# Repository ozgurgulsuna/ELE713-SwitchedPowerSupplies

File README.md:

# INTRODUCTION

This report presents the design and implementation of a forward converter that operates with an input voltage range of 36-60 V DC, providing a primary output of 5 V at 8 A along with a secondary auxiliary output of 12 V at 4 W. The forward converter is a type of DC-to-DC converter that transfers power during the forward operation of a transformer, making it suitable for applications requiring isolated and regulated outputs.

To achieve precise control over the output voltage, the design employs an analog controller integrated with a feedforward loop. The primary side of the converter utilizes a single switch, while the transformer flux is reset using an additional winding and a diode. This approach ensures efficient operation and prevents magnetic saturation of the transformer core.

In low-voltage, high-current applications, traditional diode-based rectification becomes less efficient due to the voltage drop across the diodes, typically around 0.5 V. To address this inefficiency, synchronous rectification is implemented using MOSFETs at the output. When conducting, a MOSFET with a 10-milliohm resistance produces a voltage drop of only 0.1 V at 10 A, significantly improving overall efficiency.

The printed circuit board (PCB) for this design is manufactured using a photolithography process. This process includes applying a photoresistive UV coating and etching the copper layer using a solution of hydrogen peroxide and hydrochloric acid. The circuit's functionality is thoroughly tested under various load conditions, including overload scenarios and auxiliary load operation, to validate its performance and reliability.

This report further discusses the chosen topology, magnetic design, and key considerations in achieving an efficient, compact, and robust forward converter design.

| Specification        |          |
|--------------|-------|
| Input Voltage                   | 36-60 Vdc (Nominal 48Vdc)            |
| Main Output Voltage             | 5V (min. 4.9V, max. 5.1V)            |
| Output Voltage Ripple           | 100mV peak-to-peak                   |
| Main Output Nominal Current     | 8A                                   |
| Continuous Output Power         | 40W (Main Output)                    |
| Overload Current                | 9A                                   |
| Auxiliary Output Voltage        | 12V                                  |
| Auxiliary Output Nominal Current| 0.3A                                 |
| Auxiliary Output Power          | 4W                                   |
| Line Regulation                 | $\pm 0.2$%                           |
| Load Regulation                 | $\pm 0.5$%                           |
| Transient Peak Deviation        | 10% of Vout (10% load to 100% @ 48 V) |
| Transient Response Recovery     | 200 $\mu sec$ (10% load to 100% @ 48 V) |
| Overall Efficiency @ Full Load  |$\ge$ 80%                             |

---

# TOPOLOGY
The forward converter is a widely used topology in DC-to-DC conversion, especially for applications requiring electrical isolation and multiple outputs. This topology operates by transferring energy through a transformer during the on-state of the primary-side switch, with energy delivery controlled by the duty cycle of the switch. It is a buck-type converter implemented with the output LC filter structure.

*Schematic of Forward Converter*

The duty ratio, defined as the proportion of time the primary switch is on during a switching cycle, is a critical parameter in determining the output voltage of the forward converter. The relationship between the input voltage, duty ratio, and transformer turns ratio governs the output voltage. A feedback mechanism ensures the duty ratio is adjusted dynamically to maintain a stable output under varying input and load conditions. In a forward converter, the maximum duty cycle is required to be less than 50% to ensure the transformer reset.

$${V_o \over V_i} = {Ns\over Np}*D$$

At the first cycle when the transistor T is ON, the transformer transfers power to the secondary side, and reset winding is reverse biased. In the second cycle, reset winding resets the transformer and supplies the magnetizing current back to the supply, and the load is supplied by the inductor and capacitor. Reset winding is very important to reset to transformer to prevent core saturation. In our design, we need to add two more windings to the transformer, one is to supply the primary side control circuitry, and another is to create the required 12V auxiliary supply.

The forward converter design includes a bias supply for the primary side, which provides the necessary power to the control circuitry and auxiliary components. This supply is derived from the bias winding connected to the primary side. The circuit initially starts with a voltage divider and a zener diode. As the bias winding experiences a change in flux, it supplies the rest of the circuit with the required voltage. The output of the bias winding is configured as a rectifier of a forward converter and is regulated with a linear regulator constructed from an NPN transistor. This sets the bias supply to approximately 12 volts.

*Schematic of the Bias Voltage Generation Subcircuit.*

The secondary side of the converter includes an auxiliary output in addition to the primary output. This output is set to 12 volts and is rated for 0.3 amperes, resulting in a 4 W auxiliary output. The auxiliary output is supplied from another auxiliary winding with a forward rectifier output. This output is also regulated using a 12-volt linear regulator and is referenced to the ground of the secondary winding.

*Schematic of the Auxiliary Voltage Generation Subcircuit.*

---

# MAGNETIC DESIGN

Magnetic design is a critical aspect of the forward converter, as it directly impacts efficiency, size, and reliability. The transformer in the forward converter serves two primary purposes: providing electrical isolation and stepping the voltage up or down based on the turn ratio.

A forward converter utilizes a transformer operating in forward mode, meaning that energy is transferred directly through the transformer core during the on-state of the primary switch. Unlike some other topologies, energy is not stored in the core during one cycle and transferred in the next; instead, the transfer is immediate.

The magnetic design is done in a MATLAB script that calculates key parameters for a forward converter, focusing on component sizing and operational constraints. It starts by defining input/output voltage ranges, power requirements, efficiency assumptions, and ripple constraints. The output current and its ripple are calculated to establish operating boundaries.

A significant part of the script focuses on determining the duty cycle range as a function of the transformer turns ratio $$(\N_1/N_2\)$$ and selecting an optimal ratio to ensure the converter operates within specified limits. Transformer design calculations include determining winding turns for primary, secondary, and auxiliary windings while ensuring compliance with voltage and current constraints, such as switch voltage limits. The calculated turn ratios are given in the table below.

| Winding      | Turns |
|--------------|-------|
| Primary      | 10    |
| Reset        | 10    |
| Secondary    | 4     |
| Bias         | 7     |
| Auxiliary    | 7     |

*Selected Turns Ratios.*

The script calculates the magnetizing inductance $$\(L_m\)$$ and evaluates the impact of switching frequency on inductor performance. It also designs the output filter components to meet ripple voltage constraints.

Core selection is supported by area product $$\(A_p\)$$ calculations using various methods, ensuring the chosen core can handle the required flux and thermal limits. Wire gauge and winding distribution are calculated to balance current density and copper usage.

Finally, the script includes a loss analysis, estimating core and copper losses, and evaluating leakage inductance to ensure the design meets efficiency and performance goals. This approach focuses on key aspects of forward converter design while avoiding unnecessary complexity.

The code can be found in [magnetic design folder](%5B02%5D%20Magnetic%20Design/magnetic_design.m).

## TRANSFORMER REALIZATION ##

After evaluating the available cores, calculations are made, and a few candidate cores are chosen based on area product criteria. As a final decision, E30/15/7 3C94 is chosen (by Ferroxcube). There were smaller options; however, this core is favored considering the ease of implementation. Our switching frequency is chosen as 200kHz. At 200kHz, which is moderately high, we used $1 mm^2$ litz wires to avoid the skin effect and proximity effect. For the primary we have 10 turns with no parallel wires, at the secondary, we have 4 turns with 2 parallel wires. The auxiliary winding is winded using 0.2 $mm^2$ litz cable to have lower losses. Reset winding and primary bias circuitry are winded with thin copper cables so that they won't carry high currents. The order of windings is secondary-auxiliary-reset-bias-primary.

<div style="text-align: center;">
  
  <p><em>Transformer Windings Drawing</em></p>
</div>

---
# CONTROLLER DESIGN
For the controller, a specific analog integrated circuit, LT1952-1 produced by Analog Devices, is used to implement the controller. LT 1952-1 is a single-switch synchronous forward controller for forward controller designs within the range of 25-500 W. This controller is favored because it has the option to implement synchronous rectification. and high efficiencies can be achieved. LT1952 is the main controller; however, there are 2 more integrated circuits for the essential working of the converter. TL431 is used as a feedback compensator for controlling the output voltage. Moreover, LTC3900 is used for synchronous rectification which takes the SYNC signal from the LT1952-1 with the help of pulse transformer and switches two MOSFETs for improving the efficiency (with the risk of short-circuiting the secondary side MOSFETs).

---
# PRODUCTION AND ASSEMBLED PCB
The printed circuit board (PCB) for this design is manufactured using a photolithography process. This process includes applying a photoresistive UV coating and etching the copper layer using a solution of hydrogen peroxide and hydrochloric acid. The circuit's functionality is thoroughly tested under various load conditions, including overload scenarios and auxiliary load operation, to validate its performance and reliability.

<div style="text-align: center;">
  
  <p><em>Final Results of the etched PCB.</em></p>
</div>

<div style="text-align: center;">

  <p><em>Assembled PCB</em></p>
	        
</div>

## RESULTS ##
After the design is completed and assembled some measurements are taken. At first, some problems occurred at the current sense pin of the controller, which was due to a grounding problem. We solved it by fixing it. 

*Converter Output in the case of fault.*

After fixing that, tests were continued without synchronous switches which provided an efficiency of around 75%. We activated the synchronous rectification to increase efficiency and obtain better results. At this part, we had some problems with the synchronization and failed the synchronize both switches. However, synchronizing one switch had no disadvantage but a slight improvement so we obtained a  semi-synchronous converter. Forward converter without auxiliary is quite efficient; however, the auxiliary linear regulator creates quite a loss. The results are as follows:

*5V Rated Operation*

*Voltage Ripple Measurement*

Efficiency Calculations(@48V):

Only Forward Converter

${Efficiency} = {Pout \over Pin}$ =  $`{(5.15 × 7.21) \over (48.5 × 1.04)}`$ = 0.8602

Forward Converter with 4W auxiliary load

${Efficiency} = {Pout \over Pin}$ =  $`{(5.15 × 7.21 + 4.3) \over (48.5 × 1.04)}`$ = 0.8214

I would like to point out that @60V efficiency gets worse due to auxiliary efficiency. 

---

# CONCLUSION

In conclusion, there are several isolated DC-DC converter topologies with all their advantages
and disadvantages. In this project, forward converter topology is implemented to convert 36-
60V to 5V with the addition of 12V auxiliary voltage. Moreover, the project covers magnetic design, analog design, and feedback design
for isolated DC/DC converters. The design showed that the topology proved to be working;
however, there is still room for improvement in terms of PCB design, feedback design, and
magnetic design. 

---
# APPENDIX

```matlab
close all
clear 
clc
%% Specify project requirements

Vimax = 60;
Vimin = 36;
Vo = 5;
Po = 40;
Vaux = 12;
Paux = 4;

% Choose an estimated efficiency
eff_est = 0.82;

% Choose inductor ripple ratio (ismail wants this)
ripple_ratio = 0.1625;

% Voltage ripple defined by specifications
delta_Vo = 0.1;  % Vpp

Io = Po/Vo;
Io_max = Io + Io*ripple_ratio/2;
Io_min = Io - Io*ripple_ratio/2;

% Auxiliary
Iaux = Paux/Vaux;

%% Duty Range vs Turns Ratio
% We observe the effect of turns ratio on the duty range of our converter
% given the input and output voltage range

% Calculated turns ratio for forward converter
% Vo/Vin = D*N2/N1

N1 = 1;

% We sweep N1/N2 between 1 and 5
N2 = linspace(1,5.9,50);

Dmax_vec = zeros(1,50);
Dmin_vec = zeros(1,50);

% Calculate min and max duty values for all N values
for i=1:50
    d1 = ((N2(i)) * ((Vo+Io*0.05)/Vimin));  % output inductance resistance
    d2 = ((N2(i)) * ((Vo+Io*0.05)/Vimax));
    dmax = max(d1,d2);
    dmin = min(d1,d2);
    Dmax_vec(i) = dmax;
    Dmin_vec(i) = dmin;
end

fig1 = figure;
plot(N2/N1,Dmax_vec);
hold on
plot(N2/N1,Dmin_vec);
% draw a line for the duty cycle limit
plot([0 5.9], [0.39 0.39], 'r--');
% draw a line for n = 2.6
plot([2.6 2.6], [0 0.5], 'r--');
legend
grid minor
title("Duty cycle limits vs N")
legend("D_{max}", "D_{min}")
xlabel("Turns ratio N"), ylabel("Duty cycle")
ylim([0 0.5])
hold off
% exportgraphics(fig1, "../../4-Report/img/DvsN.pdf")

% from the duty ranges we can select 
% Dmax = 0.39  and
% N1/N2 = 2.6

N2  = 1/2.6 ;
Dmax = (Vo+Io*0.05)/Vimin/N2;
%% Transformer Design
% Switch Voltage Limit: 200 V
% Vsw >= Vimax + Vimax*N1/N3 + Vsnub

Vsnub = 10 ;  % approximately
Vsw_max = 120;
N3_min = 1/((Vsw_max - Vimax - Vsnub)/(Vimax*N1));
% Vimax+Vinmax*N1/N3+Vsnub;
% N3_min = (Vsw - Vimax - Vsnub)/Vimax ;

% Dmax should be less than the Dmax level
Dmax_limit = 1/(1+N3_min/N1) ;

% Pick N3 as 1
N3 = 1;
Dmax_limit = 1/(1+N3/N1) ;

%% Determine Lm
clear dmin dmax Dmin_vec Dmax_vec d1 d2 i N
% 
Vin_vec = linspace(60, 36, 50);
D_vec = ((Vo+Io*0.05)*N1./(Vin_vec*N2));
fs = linspace(50e3, 200e3, 50);
Lmvec = zeros(1,50);
% delta_ILm_vec = ones(50, 50);  % Initial guess for delta_ILm, e.g., 0.1 A

%
Lm = 200e-6;
Fsw = 200e3;

% for i = 1:50
%     for j = 1:50
%         Lmvec(j) = Vimin*Dmax/(fs(i)*delta_ILm_vec(j))
%         delta_ILm_vec(i,j) = Vimin*Dmax/(fs(i)*Lmvec(j));
%     end
% end

% plot(fs,delta_ILm_vec)

delta_ILm = Vimin*Dmax/(Fsw*Lm);

% Choose max duty as 0.3900, calculate N
N2 = Vo/(Dmax*Vimin);

% Auxulary winding
N4 = Vaux/(Dmax*Vimin);

% Check switch peak current 
Io_pk_ref = Io_max*N2/N1/0.92;  % eff estimate correct ?
Isw_min = Io_min*N2/N1/0.92;
Isw_peak = delta_ILm+Io_pk_ref;   

% Choose switching frequency
%SOLVE DOUBLE ITERATION TO FIND DELTA IL AND LM 

% Determine the transformer current ripple

% Find required Lm versus Fsw
for i=1:50
    Lmvec(i) = (Vimin*Dmax)/(fs(i)*delta_ILm);
end

fig2= figure;
plot(fs, Lmvec/1e-6);
grid minor
xlabel("Switching Frequency (Hz)"), ylabel("L_m value (H)")
title("Lm for the ripple constraint vs. Fsw")

Ireset = (delta_ILm*(N3/N1)*Dmax)/2*1.83;

Vreset = Vimin;

%% Transformer Design POT-Core
% https://www.tdk-electronics.tdk.com/download/519704/069c210d0363d7b4682d9ff22c2ba503/ferrites-and-accessories-db-130501.pdf
Kw = 0.4;

% Select Core Material (N49)
performance_factor = 20000;

% Area Product Calculation: First Method
J = 5e6; % Current Density (A/m^2)
delta_B = performance_factor/Fsw; % Flux Density Swing (T)
P_trans = Vo*Io + Vaux*Iaux + (Vo*Io + Vaux*Iaux)/eff_est+ Vreset*Ireset; % Transmitted Power (P)

% First Ap is from the lecture notes
% Area Product Calculation: Method-1
display("Method-1")
Ap = ((11.1*Vo*Io/eff_est)/(0.141*delta_B*Fsw))^(1.31)*1e4

% Area Product Calculation: Method-2
display("Method-2")
Ap = ((Vo*Io/eff_est)/(0.014*delta_B*Fsw))^(4/3)*1e4

% Area Product Calculation: Method-3
display("Method-3")
C = 0.71; % Converter Coefficient (Forward Converter)
Ap = P_trans/(C*delta_B*Fsw*J)*1e12

% Area Product Calculation: Method-4
display("Method-4")
Kconv = 0.5;
Ap = Kconv*P_trans/(Kw*Fsw*delta_B*J)*1e12

% Selected RM type Core (RM 8 N49)
Ac = 64e-6;
Aw = 10.8*(17-8.55)/2e6;
Ap_core_rm8 = Ac*Aw*1e12
Al = 2200; % (nH/N^2)

% % Selected RM type Core (RM 7 N49 )
% Ac = 43e-6;
% Aw = 8.4*(14.75-7.25)/2e6;
% Ap_core_rm7 = Ac*Aw*1e12
% Al = 1900; % (nH/N^2)

% Ac = 31.3e-6;
% Aw = 8*(12.6-6.4)/2e6;
% Ap_core_rm6 = Ac*Aw*1e12
% Al = 2400; % (nH/N^2)

% % Selected ETD type Core (E 20/10/6 EF20)
% Ac = 32e-6;
% Aw = 14*(14.1-5.9)/2e6;
% Ap_core = Ac*Aw
 
% % Selected PQ type Core (PQ20/20)
% Ac = 62.1e-6;
% Aw = 14.3*(18-8.8)/2e6;
% Ap_core = Ac*Aw
% Al = 5200 % (nH/N^2)

% % RM 10 N49
% Ac = 98e-6;
% Aw = 12.4*(21.2-10.9)/2e6;
% Ap_core = Ac*Aw*1e12
% Al = 2900; % (nH/N^2)

% 
% % RM 12
% Ac = 146e-6;
% Aw = 16.8*(25-12.8)/2e6;
% Ap_core = Ac*Aw
% Al = 5300; % (nH/N^2)

% % EFD 20/10/7
% Ac = 31e-6;
% Aw = 7.77*2*(15.4-8.9)/2;
% Ap_core = Ac*Aw*1e12
% Al = 910;

% % ETD 34/17/11
% Ac = 97.1e-6;
% Aw = 11.8*2*(25.6-11.1)/2e6;
% Ap_core_ETD = Ac*Aw*1e12
% Al = 2600;

% % P18/11 SER
% Ac = 43.3e-6;
% Aw = (14.9-7.60)/2*7.2/1e6;
% Ap_core_P18 = Ac*Aw*1e12
% Al = 260;

% % EF 25 6 11 N97
% Ac = 67.2e-6;
% Aw = (21.7-9.4)/2*6.2/1e6;
% Ap_core_EF25 = Ac*Aw*1e12
% Al = 4100;

% E30/15/7 3C94
Ac = 60e-6;
Aw = (19.5-7.2)/2*9.7*2/1e6;
Ap_core_E30 = Ac*Aw*1e12
Al = 1900;

% % E20/10/6
% Ac = 32e-6;
% Aw = (14.1-5.9)/2*7*2/1e6;
% Ap_core_E20 = Ac*Aw*1e12
% Al = 1350;

%% Turn Number and Saturation Calculations
% From primary side 
% Vp = N1 dΦ/dt

% Expected operation
Np = (Vimax)*D_vec(1)/(Fsw*delta_B*Ac);
Np = (Vimin)*Dmax/(Fsw*delta_B*Ac)

% At max instance, allow for max B. if turns ratio higher than this, core
% will not saturate.
B_sat = 0.3;

% Min turn numbers, less than that with saturate the core 
Np_min = (Vimax)*0.5/(Fsw*B_sat*Ac) 

Np = 10
Nr = 10

Ns_min = Np*N2
Naux_min = Np*N4

Ns = 4
Na = 10

% Np = 8  PRIMARY
% Nr = 8  RESET
% Ns = 3  SECONDARY
% Na = 6  AUX

% Let's back-calculate the core flux density
% Lm = Np dΦ/i in microhenries
Lm_core = Al*Np*Np*1e-9

% in Tesla
delta_B_core = Lm*delta_ILm/(Np*Ac)

% in Tesla
delta_B_core = Lm_core*delta_ILm/(Np*Ac) 

%% Wire Gauge Calculation
% Determine Cable Length and Type
% https://masteringelectronicsdesign.com/the-rms-value-of-a-trapezoidal-waveform-part-2/
% https://masteringelectronicsdesign.com/how-to-derive-the-rms-value-of-a-triangle-waveform/
% Primary side assume square type voltage

Isw_mean = (Isw_peak+Isw_min)/2;
Isw_rms = Isw_mean*sqrt(Dmax);
Isw_rms = sqrt(Dmax/3*(Isw_peak^2+Isw_peak*Isw_min+Isw_min^2));

Isw_avg = Isw_mean*Dmax

Ipri_rms = Isw_rms;
Isec_rms = sqrt(Dmax/3*(Io_max^2+Io_max*Io_min+Io_min^2))

Ireset_rms = delta_ILm*(N3/N1)*sqrt(Dmax/3);

Iaux_rms = sqrt(Dmax/3*((Iaux*1.2)^2+Iaux^2+(Iaux*0.9)^2))

% Winding Area Distribution

A1 = Ipri_rms*Np
A2 = Isec_rms*Ns
A3 = Ireset_rms*Nr
A4 = Iaux_rms*Na

Atotal = A1 + A2 + A3 + A4

A1 = A1/Atotal
A2 = A2/Atotal
A3 = A3/Atotal
A4 = A4/Atotal

Pri_copper_cs = A1*Kw*Aw/Np*1e6
Sec_copper_cs = A2*Kw*Aw/Ns*1e6
Reset_copper_cs = A3*Kw*Aw/Nr*1e6
Aux_copper_cs = A4*Kw*Aw/Na*1e6

Jp=Ipri_rms/Pri_copper_cs
Js=Isec_rms/Sec_copper_cs
Jr=Ireset_rms/Reset_copper_cs
Ja=Iaux_rms/Aux_copper_cs

%% Litz
% Determine Cable Length and Type

% Set cable diameters:

% https://www.elektrisola.com/en/Litz-Wire/Info
litz_packing_factor = 1.28 ;

% TO DO: winding configuration sec/2 : pri : sec/2

%% Output Filter Calculation

Cf_cross_Lf = (Vo*(1-D_vec(1)))/(Fsw^2*8*delta_Vo) 

Lf = 16e-6 % SRP1265CC-220M reduces to 16 uH @ 10 A
Cf_min = Cf_cross_Lf/Lf

Cf = (5 + 5 + 5)*1e-6 ; % uF

delta_Vo_calculated = ((1-D_vec(1)))/(8*Lf*Cf*Fsw^2)*Vo;

delta_Il_max = ((Ns/Np*Vimax-Vo)*(Dmax)/(Fsw*Lf))
delta_Il = ((Ns/Np*Vimax-Vo)*(D_vec(1))/(Fsw*Lf))
Il_peak = Po/Vo+delta_Il/2

Caux_cross_Laux = (Vaux*(1-D_vec(1)))/(Fsw^2*8*Vaux*0.2);
Laux = 2.2e-6;
Caux_min = Caux_cross_Laux/Laux;
Caux = (5 + 5)*1e-6 ; % uF

delta_Iaux_max = ((Vaux)*(1-Dmax)/(Fsw*Laux))  %% simulation check

%% Power Loss

% Core Loss
% https://elnamagnetics.com/wp-content/uploads/library/Ferroxcube-Materials/3C94_Material_Specification.pdf

% Coefficients (with 95% confidence bounds):
p1 =   8.892e-05;
p2 =     0.01501;
p3 =      -0.775;
p4 =       17.63;

P_density_center = p1.*(B_field_center.*1000.*ripple_ratio).^3 + p2.*(B_field_center.*1000.*ripple_ratio).^2 + p3.*(B_field_center.*1000.*ripple_ratio) + p4; % mT -> kW per m^3
P_center = P_density_center.*(C*D*F*2)*1000 ;% core center volume

P_density_sides = p1.*(B_field_sides.*1000.*ripple_ratio).^3 + p2.*(B_field_sides.*1000.*ripple_ratio).^2 + p3.*(B_field_sides.*1000.*ripple_ratio) + p4; % mT -> kW per m^3
P_sides = P_density_sides.*(((A-B)*F*2*D)+((B-C)*(D-E)*F*2))*1000 ;  % core center volume

P_core = (P_center + P_sides)*2 ; % an error margin of 200 % is given

% Copper Loss for litz wire
% AC losses proximity and skin effect can be ignored
% Length of the wires is estimated from the middle radius

end_winding_pri = 0.265;
end_winding_sec = 0.080;

lenght_pri = primary_cable_count*(2*(C+0.005+primary_cable_diameter/2)+2*(F+0.005+primary_cable_diameter/2));
lenght_sec = secondary_cable_count*(((A+B)/2*2)+(5e-3+F)*2) ;

R_meas_pri = 18e-3;
R_pri = (cu_resistivity*lenght_pri)/(primary_parallel*pi*(primary_cable_diameter/2)^2*primary_parallel/litz_packing_factor);
R_pri = R_meas_pri*lenght_pri/(lenght_pri+end_winding_pri);

R_meas_sec = 102e-3;
R_sec = (cu_resistivity*lenght_sec)/(secondary_parallel*pi*(secondary_cable_diameter/2)^2*secondary_parallel/litz_packing_factor);
R_sec = (R_meas_sec*lenght_sec/secondary_parallel)/(lenght_sec/secondary_parallel+end_winding_sec)

P_cu_pri = R_pri*5.3*5.3;
P_cu_sec = R_sec*1.45*1.45;

P_cu_total = P_cu_pri + P_cu_sec ;

% https://downloads.hindawi.com/archive/2012/635715.pdf
L_leak = (mu0*N_pri^2*((0.00016)*2+((B-C)/2))*(F*E+D*(C+2*(((B-C)/2)))))/(3*2^2*E^2);
```

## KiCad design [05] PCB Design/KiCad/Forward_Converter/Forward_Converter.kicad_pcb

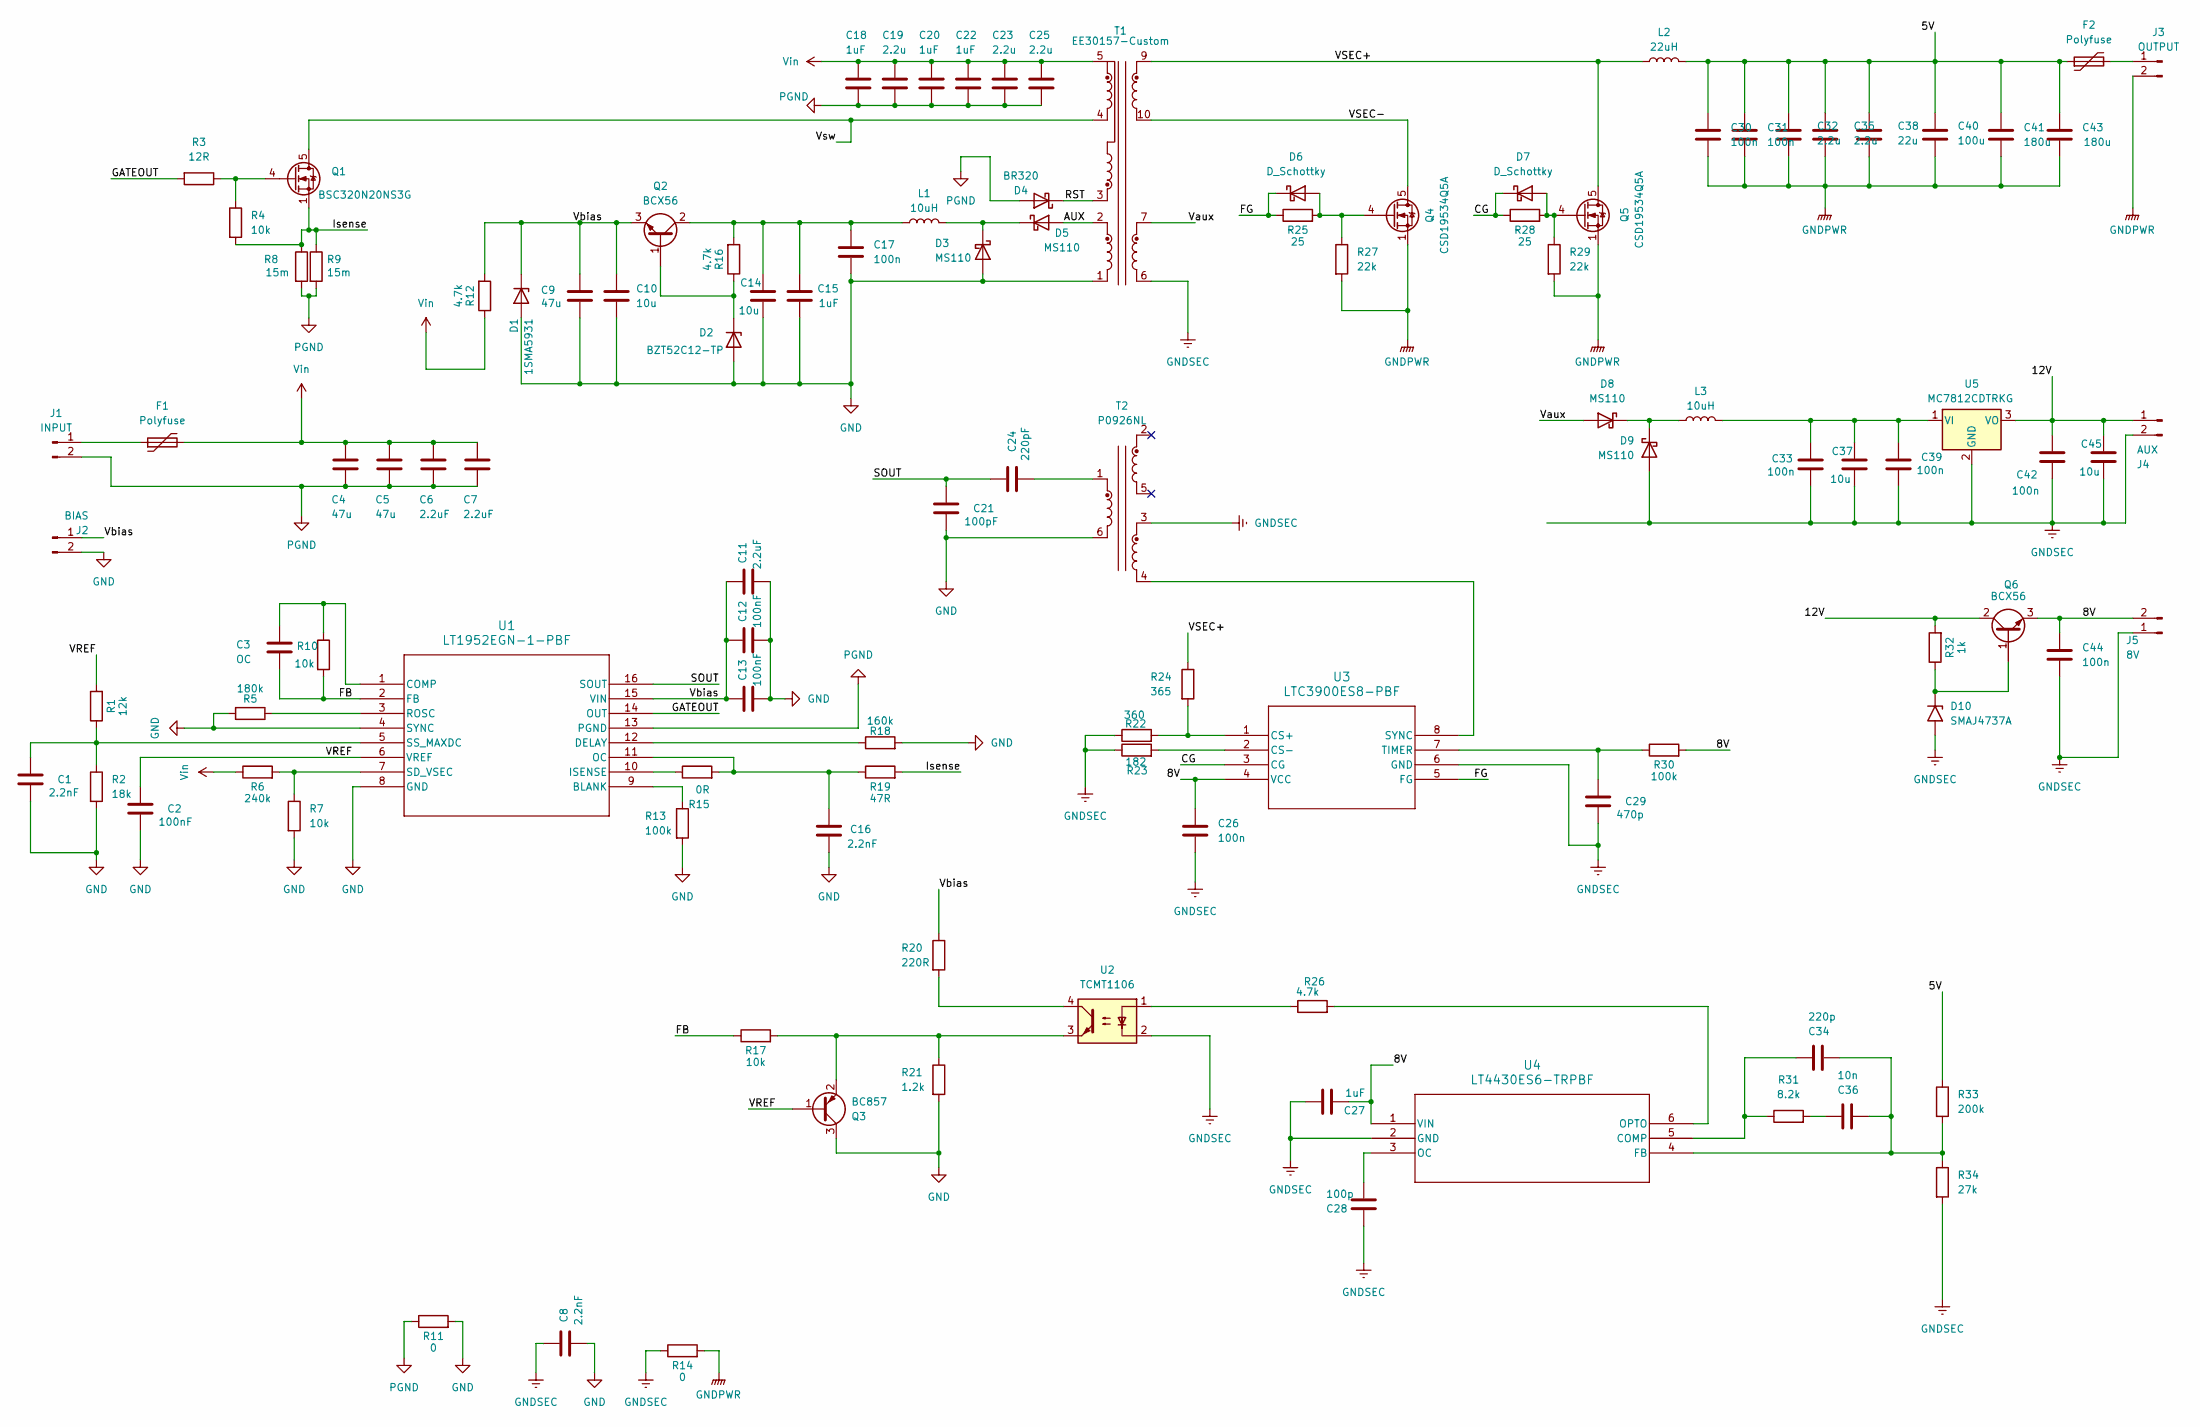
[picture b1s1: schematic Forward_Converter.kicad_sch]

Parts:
C1, C8, C16: 2.2nF; C_0805_2012Metric
C2, C12, C13: 100nF; C_0805_2012Metric
C3: OC; C_0805_2012Metric
C4, C5, C9: 47u; CP_Elec_10x12.6
C6, C7: 2.2uF; C_2220_5750Metric
C10, C14, C37, C45: 10u; C_1210_3225Metric
C11: 2.2uF; C_0805_2012Metric
C15, C18, C20, C22: 1uF; C_1210_3225Metric
C17, C26, C30, C31, C33, C39, C42, C44: 100n; C_0805_2012Metric
C19, C23, C25, C32, C35: 2.2u; C_2220_5750Metric
C21: 100pF; C_1206_3216Metric
C24: 220pF; C_1206_3216Metric
C27: 1uF; C_0805_2012Metric
C28: 100p; C_0805_2012Metric
C29: 470p; C_0805_2012Metric
C34: 220p; C_0805_2012Metric
C36: 10n; C_0805_2012Metric
C38: 22u; C_1210_3225Metric
C40: 100u; D_SMC
C41, C43: 180u; CP_Elec_10x12.6
D1: 1SMA5931; D_SMA
D2: BZT52C12-TP; D_SOD-123
D3, D5, D8, D9: MS110; D_SMA
D4: BR320; D_SMB
D6, D7: D_Schottky; D_SOD-123
D10: SMAJ4737A; D_SMA
F1, F2: Polyfuse; 0154010.DR
J1: INPUT; PhoenixContact_MSTBA_2,5_2-G-5,08_1x02_P5.08mm_Horizontal
J2: BIAS; PinHeader_1x02_P2.54mm_Vertical
J3: OUTPUT; TerminalBlock_MetzConnect_Type086_RT03402HBLC_1x02_P3.81mm_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
J4: AUX; TerminalBlock_MetzConnect_Type086_RT03402HBLC_1x02_P3.81mm_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
J5: 8V; PinHeader_1x02_P2.54mm_Vertical
L1, L3: 10uH; IND_VLS6045EX-100M-H
L2: 22uH; SRP1513CA8R2M_V2
Q1: BSC320N20NS3G; TDSON-8-1
Q2, Q6: BCX56; SOT-89-3
Q3: BC857; SOT-23
Q4, Q5: CSD19534Q5A; TDSON-8-1
R1: 12k; R_0805_2012Metric
R2: 18k; R_0805_2012Metric
R3: 12R; R_0805_2012Metric
R4, R7, R10, R17: 10k; R_0805_2012Metric
R5: 180k; R_0805_2012Metric
R6: 240k; R_0805_2012Metric
R8, R9: 15m; R_2512_6332Metric
R11, R14: 0; R_0805_2012Metric
R12, R16, R26: 4.7k; R_0805_2012Metric
R13, R30: 100k; R_0805_2012Metric
R15: 0R; R_0805_2012Metric
R18: 160k; R_0805_2012Metric
R19: 47R; R_0805_2012Metric
R20: 220R; R_0805_2012Metric
R21: 1.2k; R_0805_2012Metric
R22: 360; R_1206_3216Metric
R23: 182; R_1206_3216Metric
R24: 365; R_1206_3216Metric
R25, R28: 25; R_0805_2012Metric
R27, R29: 22k; R_0805_2012Metric
R31: 8.2k; R_0805_2012Metric
R32: 1k; R_0805_2012Metric
R33: 200k; R_0805_2012Metric
R34: 27k; R_0805_2012Metric
T1: EE30157-Custom
T2: P0926NL; Pulse_P0926NL
U1: LT1952EGN-1-PBF; SOP16 DIP Adapter
U2: TCMT1106; SOP-4_4.4x2.6mm_P1.27mm
U3: LTC3900ES8-PBF; SO-8_S_LIT
U4: LT4430ES6-TRPBF; TSOT-23_S6_LIT-M
U5: MC7812CDTRKG; TO-252-2

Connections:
/5V: C30.1, C31.1, C32.1, C35.1, C38.1, C40.1, C41.1, C43.1, F2.1, L2.2, R33.1
/8V: C26.1, C27.1, C44.1, J5.2, Q6.3 (E), R30.2, U3.4 (VCC), U4.1 (VIN)
/12V: C42.1, C45.1, J4.1, Q6.2 (C), R32.2, U5.3 (VO)
/AUX: D5.2 (A), T1.2
/CG: D7.1 (K), R28.1, U3.3 (CG)
/FB: C3.1, R10.2, R17.1, U1.2 (FB)
/FG: D6.1 (K), R25.1, U3.5 (FG)
/GATEOUT: R3.2, U1.14 (OUT)
/Isense: Q1.1 (S), Q1.2 (S), Q1.3 (S), R4.2, R8.1, R9.1, R19.2
/RST: D4.1 (K), T1.3
/SOUT: C21.2, C24.2, U1.16 (SOUT)
/VREF: C2.2, Q3.1 (B), R1.2, U1.6 (VREF)
/VSEC+: L2.1, Q5.5 (D), R24.1, T1.9
/VSEC-: Q4.5 (D), T1.10
/Vaux: D8.2 (A), T1.7
/Vbias: C9.1, C10.1, C11.2, C12.2, C13.2, D1.1 (K), J2.1, Q2.3 (E), R12.2, R20.1, U1.15 (VIN)
/Vsw: Q1.5 (D), T1.4
GND: C1.1, C2.1, C8.1, C9.2, C10.2, C11.1, C12.1, C13.1, C14.2, C15.2, C16.1, C17.2, C21.1, D1.2 (A), D2.2 (A), D3.2 (A), J2.2, Q3.3 (C), R2.2, R5.2, R7.2, R11.2, R13.2, R18.2, R21.2, T1.1, T1.8, T2.6, U1.4 (SYNC), U1.8 (GND)
GNDPWR: C30.2, C31.2, C32.2, C35.2, C38.2, C40.2, C41.2, C43.2, J3.2, Q4.1 (S), Q4.2 (S), Q4.3 (S), Q5.1 (S), Q5.2 (S), Q5.3 (S), R14.2, R27.2, R29.2
GNDSEC: C8.2, C26.2, C27.2, C28.2, C29.1, C33.2, C37.2, C39.2, C42.2, C44.2, C45.2, D9.2 (A), D10.2 (A2), J4.2, J5.1, R14.1, R22.1, R23.1, R34.2, T1.6, T2.3, U2.2, U3.6 (GND), U4.2 (GND), U5.2 (GND)
unnamed: C24.1, T2.1
unnamed: C36.2, R31.2
unnamed: D2.1 (K), Q2.1 (B), R16.1
unnamed: D3.1 (K), D5.1 (K), L1.2
unnamed: D6.2 (A), Q4.4 (G), R25.2, R27.1
unnamed: D7.2 (A), Q5.4 (G), R28.2, R29.1
unnamed: D8.1 (K), D9.1 (K), L3.1
unnamed: D10.1 (A1), Q6.1 (B), R32.1
unnamed: F1.1, J1.1
unnamed: F2.2, J3.1
unnamed: Q1.4 (G), R3.1, R4.1
unnamed: C14.1, C15.1, C17.1, L1.1, Q2.2 (C), R16.2
unnamed: Q3.2 (E), R17.2, R21.1, U2.3
unnamed: R20.2, U2.4
unnamed: R26.1, U2.1
unnamed: R13.1, U1.9 (BLANK)
unnamed: C3.2, R10.1, U1.1 (COMP)
unnamed: R18.1, U1.12 (DELAY)
unnamed: R15.1, U1.10 (ISENSE)
unnamed: C16.2, R15.2, R19.1, U1.11 (OC)
unnamed: R5.1, U1.3 (ROSC)
unnamed: R6.2, R7.1, U1.7 (SD_VSEC)
unnamed: C1.2, R1.1, R2.1, U1.5 (SS_MAXDC)
unnamed: R22.2, R24.2, U3.1 (CS+)
unnamed: R23.2, U3.2 (CS-)
unnamed: T2.4, U3.8 (SYNC)
unnamed: C29.2, R30.1, U3.7 (TIMER)
unnamed: C34.2, R31.1, U4.5 (COMP)
unnamed: C34.1, C36.1, R33.2, R34.1, U4.4 (FB)
unnamed: C28.1, U4.3 (OC)
unnamed: R26.2, U4.6 (OPTO)
unnamed: C33.1, C37.1, C39.1, L3.2, U5.1 (VI)
PGND: C4.2, C5.2, C6.2, C7.2, C18.2, C19.2, C20.2, C22.2, C23.2, C25.2, D4.2 (A), J1.2, R8.2, R9.2, R11.1, U1.13 (PGND)
Vin: C4.1, C5.1, C6.1, C7.1, C18.1, C19.1, C20.1, C22.1, C23.1, C25.1, F1.2, R6.1, R12.1, T1.5

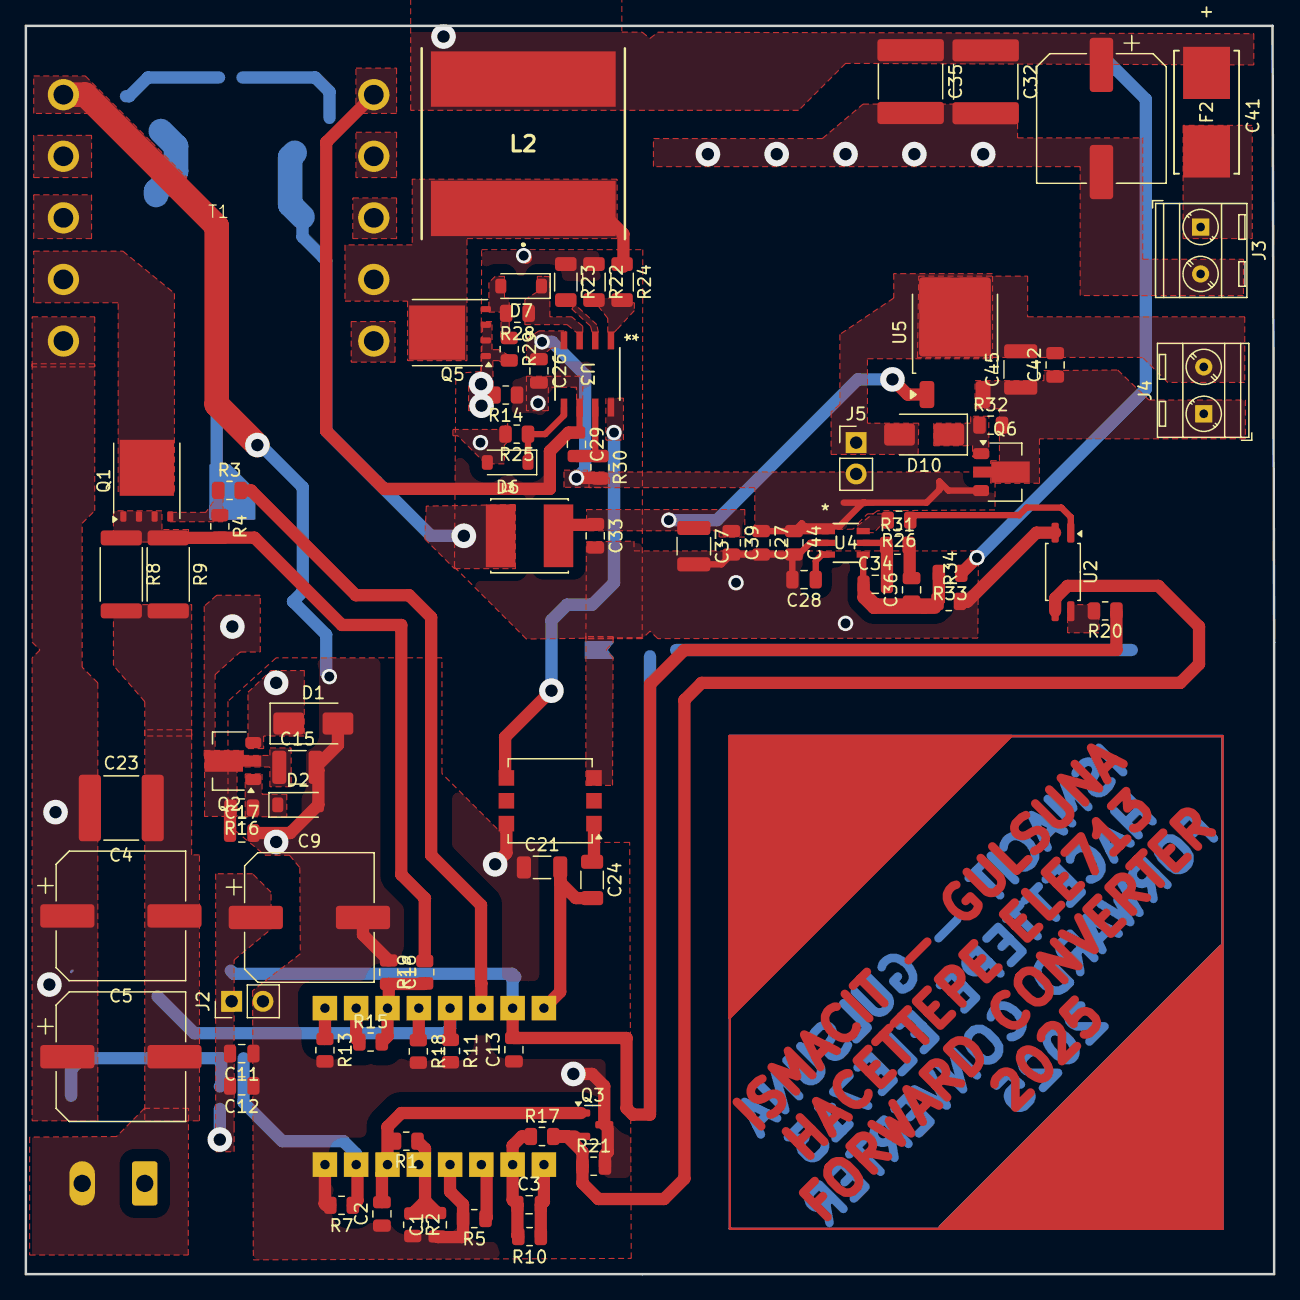
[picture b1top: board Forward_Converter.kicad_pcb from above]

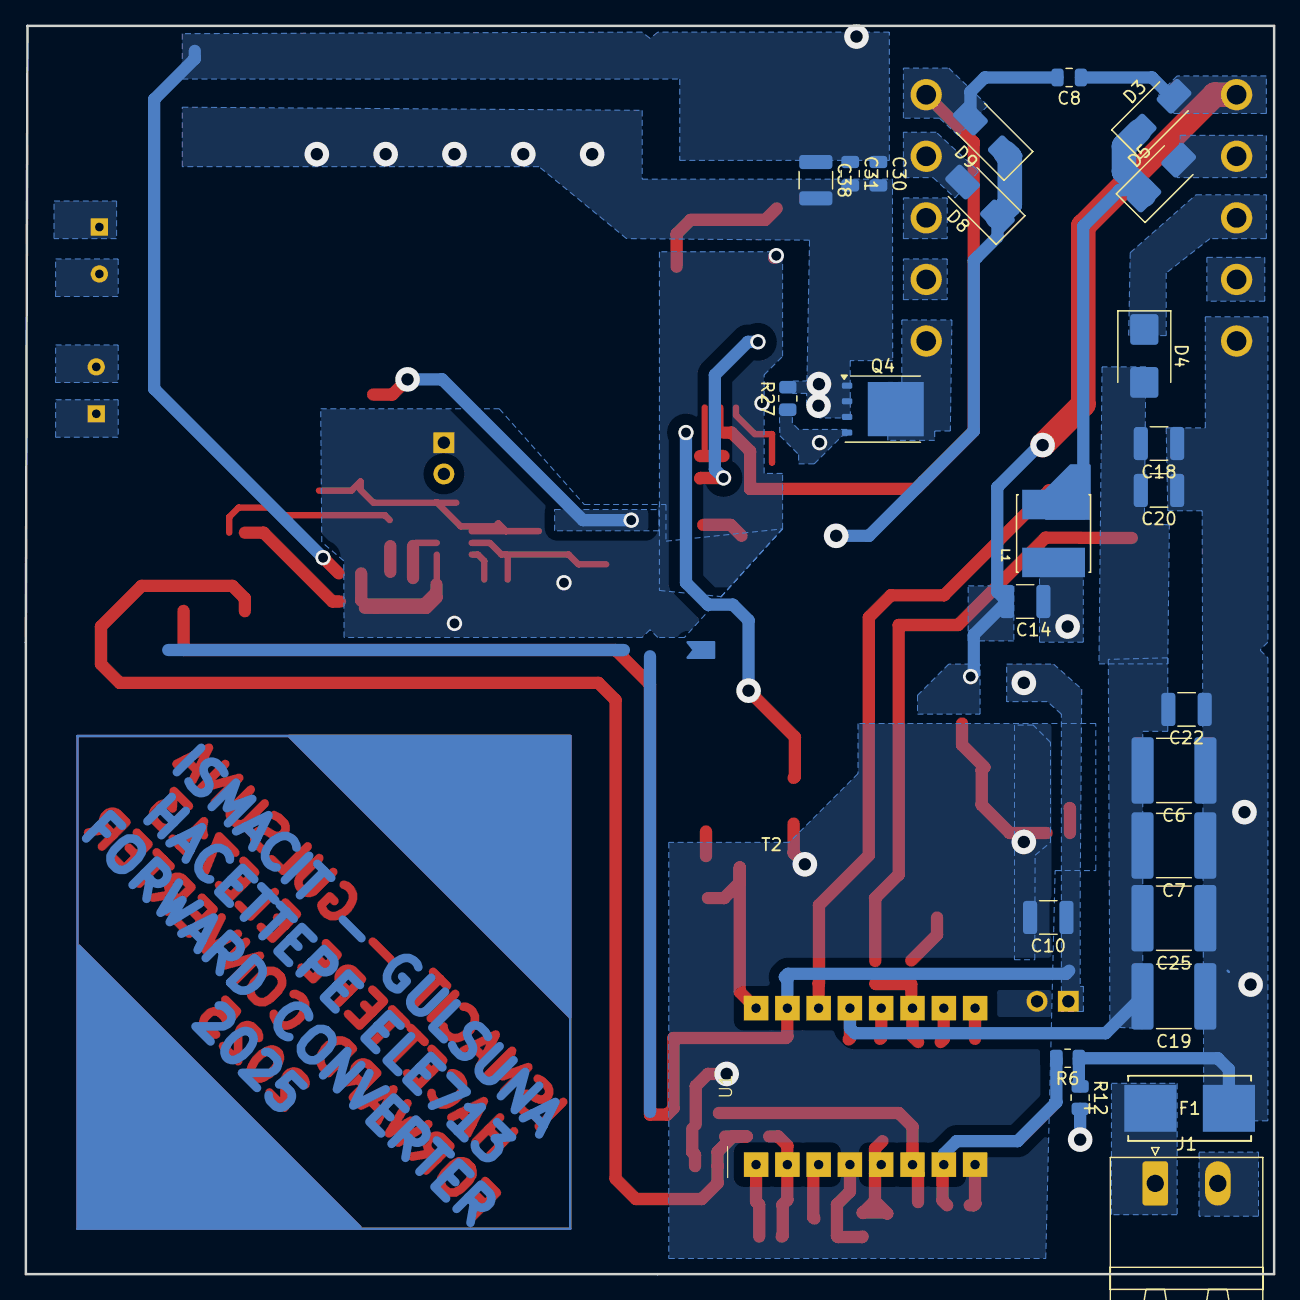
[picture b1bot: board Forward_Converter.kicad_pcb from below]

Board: 2 copper layers, 101.3 x 101.3 mm, 110 parts (26 on the bottom side), 54 nets.

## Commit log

2024-11-25 [02] % Duty Range vs Turns Ratio %
2024-11-26 [02] % Reset Winding
2024-11-26 [03] Forward Converter Sim
2024-11-28 [02] % Efficiency accounted for ?
2024-11-28 [03] Forward Conv. Parameters
2024-12-01 [02] % not completed
2024-12-01 [02] % TX design is about to finish
2024-12-01 [03] Sim files for latest design
2024-12-01 [02] % switch current is now an output (just to check)
    Also do not forget to iteratively solve delta_ILm, Lm and fsw relation.
2024-12-02 [04] Documents, DataBook and Design
2024-12-02 [02] % design update with np = 8 and ns = 3
2024-12-21 [02] Magnetic Design Finalized
2024-12-21 [03] open loop sim. completed
2024-12-23 [05] Hardware List
2024-12-23 [01] Controller Design Progress
2024-12-23 [04] Things to do
2024-12-24 Sheet 3 Yerli Parçalar
    Added new sheet for Özdisan components
2024-12-25 Update Hardware List
    More components are added
2024-12-26 [05] Bom update from local sellers
2024-12-26 Added Purchased Components
    Excel files is updated accordingly, purchased components are added.
2024-12-29 [02] Magnetic design, new cores
2024-12-31 PCB Documents Inıtial Commit
2025-01-01 Schematic and symbols are added
    Transformer footprint is missing and controller card needs attention
2025-01-01 [03] Close-loop simulation with LT1952-1
2025-01-01 [02][03] Sim faulty / magnetic design updated
2025-01-01 [03] Simulation to be improved
2025-01-02 [03][02] Controller designed / Sim. working
2025-01-02 Schematic update
    IC's are updated, transformer is added
2025-01-02 [03] secondary bias supply
2025-01-03 [03] Close-loop realistic model kind of working
2025-01-03 [03] a better realistic sim
2025-01-03 [03] 10 % to 100 %
2025-01-03 [03] Synchronous Rectification
2025-01-03 [03] reorder relocation
2025-01-03 Schematic Update
    Almost Complete
2025-01-03 [03] completely done
    finito
2025-01-03 Schematic Final with footprints
    Layout to be done
2025-01-04 Layout placement
    Placement is almost complete connections to be completed.
2025-01-04 [05] schematic with zero percent battery
2025-01-04 Layout is updated
    Close to the final result
2025-01-07 [05] PCB finalized
2025-01-10 [05] Sync Resistor added
    Sync Resistor added
2025-01-11 Simulation Update with TL431
2025-01-11 Simulation Update
    Simulation Update added bullshit
2025-01-16 Report Update
    Introduction, Topology and Magnetic Design
2025-01-16 Converter photo and specifications template
2025-01-16 Magnetic Design Report Update
2025-01-16 Magnetic design code added to the report
2025-01-16 V_bias subcircuit on report
2025-01-16 Turns ratio table generation in report
2025-01-16 Table caption update report
2025-01-16 Controller and Transformer Report
2025-01-16 Specs are added details are on the way
2025-01-16 Added PCB Images Update
2025-01-16 Title update on report
2025-01-16 Small updates on equations on report
2025-01-16 Results and Conclusion Updated

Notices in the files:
parts and their libraries:
Copyright 2016 Accelerated Designs. All rights reserved.
